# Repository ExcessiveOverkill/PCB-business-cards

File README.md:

# Persistence of vision display business cards

PCB cards designed for opensauce 2024 to give out to people

## Who is this repo for?
Anyone looking to make these cards for themselves or their own business.
It is NOT for people looking to make and sell the cards to others. (non-commercial use only)

## Software
- STM32CubeIDE
- python (numpy, cv2)
- Visual Studio Code

## Assembly
### The boards themselves
I ordered my PCBs from PCB way with .8mm thickness and ENIG coating since it is important to have a good contact surface for the batteries (and it looks nicer than HASL)

### Components
> [!WARNING]
> These exact parts I ordered in bulk from LCSC.
> The parts below are the closest matches I could find from DigiKey, but have not been tested yet

A DigiKey cart containing all of the needed components can be found [here](https://www.digikey.com/en/mylists/list/D8ND2J1IRM)
> [!IMPORTANT]
> The battery clips I used were from LCSC not DigiKey. The ones in the digikey cart have a slightly different footprint and may not fit perfectly.
> The exact clips I used can be found [here](https://www.lcsc.com/product-detail/Button-And-Strip-Battery-Connector_MYOUNG-MY-2032-30_C7525432.html)

Two standard CR2032 batteries are required, I used the cheap amazon ones.

### Placement
An interactive BOM can be found [here](opensauce2024/bom/ibom.html) (open in browser)

### Soldering
These boards are NOT designed to be hand-solderable.

I highly recommend at least a hotplate.

A stencil could be purchaced from a PCB manufacturer to make placing the solder paste easier, but it is not requred. (PCB and stencil files are in the repo)

The accelerometer is very susceptible to bad solder joints and will result in the card not activating when shaken. I had to resolder many of them to fix this.

## Programming
### Generating the graphics
Run "imageConverter.py", select which images or animations you want to display normally.

A second file select window will open for SECRET images to display. They will be displayed randomly according to the parameters set at the top of the python file.

Simply don't select anything if you do not want a secret image.

Images should be 32 pixel high PNGs, width does not matter, the card will show the entire image.

Once the images are selected, the program will show a demo of what will be displayed then write to a file defining the frame data.

### Programming the card
After the graphics have been saved, you simply build and upload the STM32 project using STM32CubeIDE.

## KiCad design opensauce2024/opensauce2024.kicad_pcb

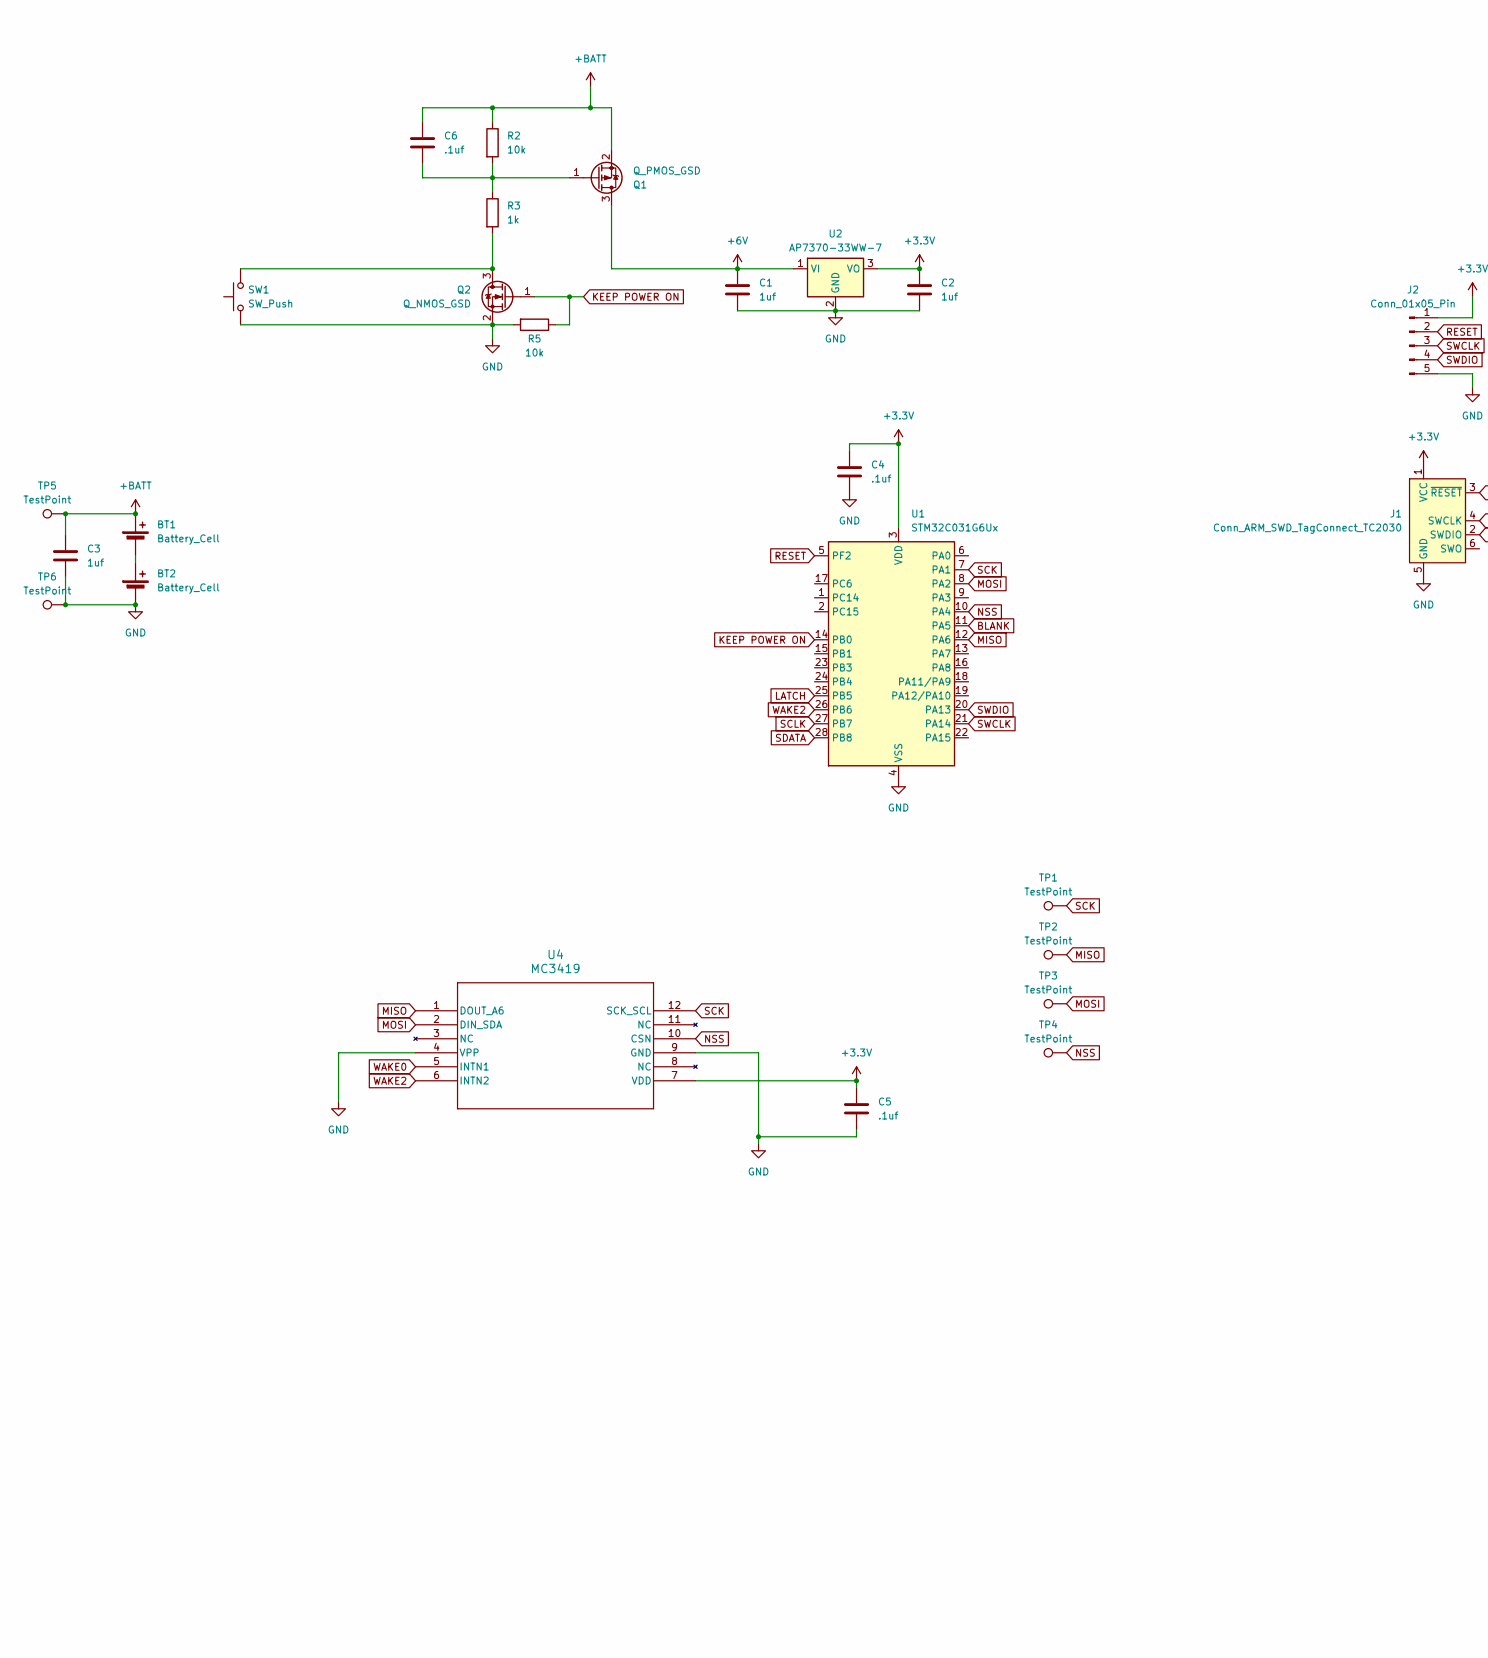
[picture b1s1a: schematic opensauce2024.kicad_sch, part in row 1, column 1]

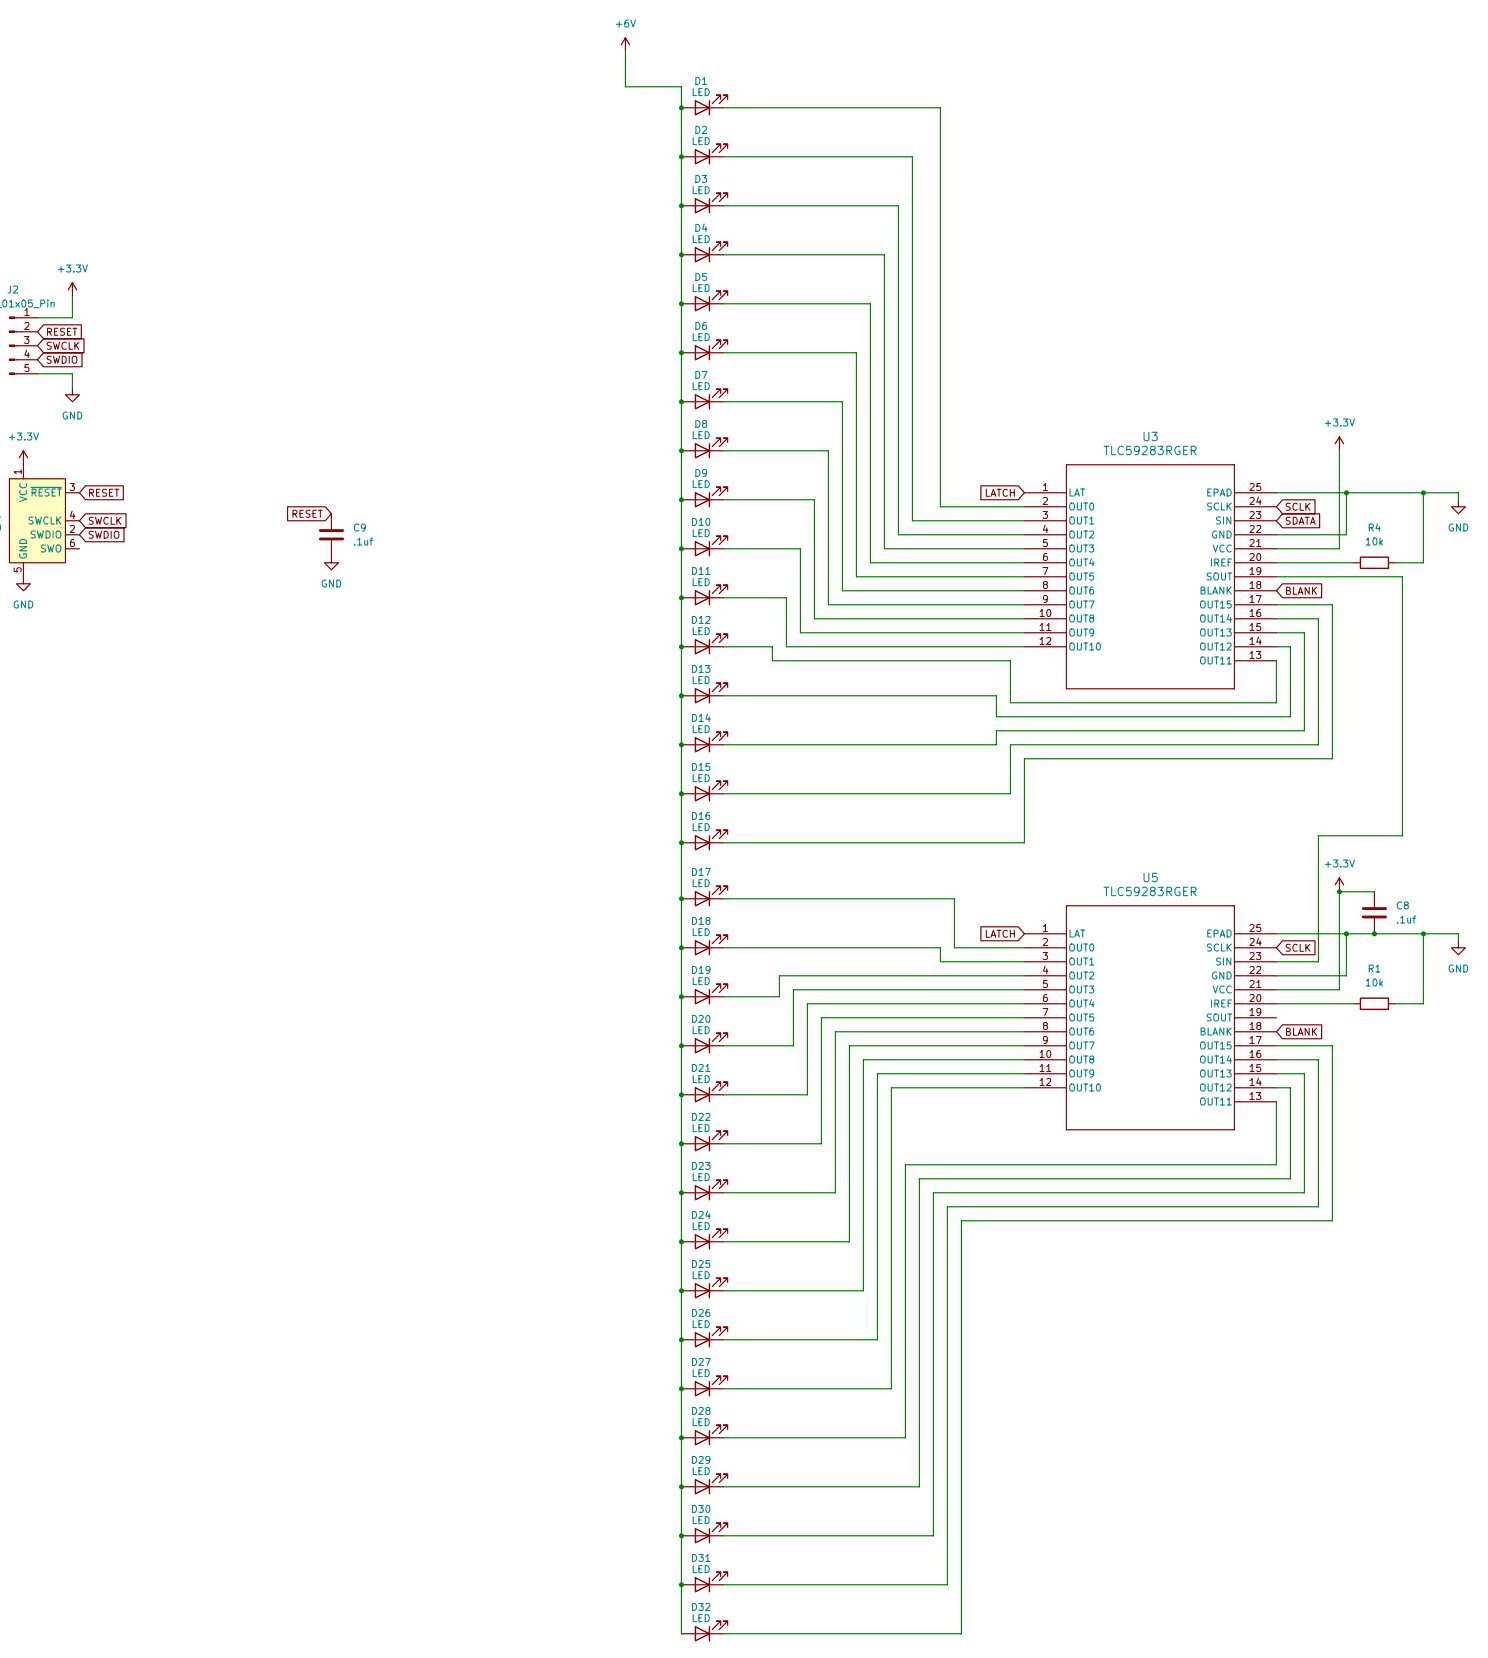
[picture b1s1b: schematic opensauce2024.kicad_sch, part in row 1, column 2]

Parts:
BT1, BT2: Battery_Cell; cr2032
C1, C2, C3: 1uf; C_0603_1608Metric
C4, C5, C6, C8, C9: .1uf; C_0603_1608Metric
D1, D2, D3, D4, D5, D6, D7, D8, D9, D10, D11, D12, D13, D14, D15, D16, D17, D18, D19, D20, D21, D22, D23, D24, D25, D26, D27, D28, D29, D30, D31, D32: LED; LED_0603_1608Metric
J1: Conn_ARM_SWD_TagConnect_TC2030; Tag-Connect_TC2030-IDC-FP_2x03_P1.27mm_Vertical
J2: Conn_01x05_Pin; PinHeader_1x05_P2.54mm_Vertical
Q1: Q_PMOS_GSD; SOT-23
Q2: Q_NMOS_GSD; SOT-23
R1, R2, R4, R5: 10k; R_0603_1608Metric
R3: 1k; R_0603_1608Metric
SW1: SW_Push; SW_Push_1P1T_XKB_TS-1187A
TP1, TP2, TP3, TP4: TestPoint; TestPoint_Pad_D1.0mm
TP5, TP6: TestPoint; TestPoint_Pad_D2.0mm
U1: STM32C031G6Ux; QFN-28_4x4mm_P0.5mm
U2: AP7370-33WW-7; SOT25
U3, U5: TLC59283RGER; RGE24_2P1X2P1_TEX
U4: MC3419; LGA-12_2x2mm_P0.5mm

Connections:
+3.3V: C2.1, C4.1, C5.1, C8.1, J1.1 (VCC), J2.1, U1.3 (VDD), U2.3 (VO), U3.21 (VCC), U4.7 (VDD), U5.21 (VCC)
+6V: C1.1, D1.2 (A), D2.2 (A), D3.2 (A), D4.2 (A), D5.2 (A), D6.2 (A), D7.2 (A), D8.2 (A), D9.2 (A), D10.2 (A), D11.2 (A), D12.2 (A), D13.2 (A), D14.2 (A), D15.2 (A), D16.2 (A), D17.2 (A), D18.2 (A), D19.2 (A), D20.2 (A), D21.2 (A), D22.2 (A), D23.2 (A), D24.2 (A), D25.2 (A), D26.2 (A), D27.2 (A), D28.2 (A), D29.2 (A), D30.2 (A), D31.2 (A), D32.2 (A), Q1.3 (D), U2.1 (VI)
+BATT: BT1.1 (+), C3.1, C6.1, Q1.2 (S), R2.1, TP5.1
BLANK: U1.11 (PA5), U3.18 (BLANK), U5.18 (BLANK)
GND: BT2.2 (-), C1.2, C2.2, C3.2, C4.2, C5.2, C8.2, C9.2, J1.5 (GND), J2.5, Q2.2 (S), R1.2, R4.2, R5.2, SW1.1, TP6.1, U1.4 (VSS), U2.2 (GND), U3.22 (GND), U3.25 (EPAD), U4.4 (VPP), U4.9 (GND), U5.22 (GND), U5.25 (EPAD)
KEEP POWER ON: Q2.1 (G), R5.1, U1.14 (PB0)
LATCH: U1.25 (PB5), U3.1 (LAT), U5.1 (LAT)
MISO: TP2.1, U1.12 (PA6), U4.1 (DOUT_A6)
MOSI: TP3.1, U1.8 (PA2), U4.2 (DIN_SDA)
NSS: TP4.1, U1.10 (PA4), U4.10 (CSN)
unnamed: BT1.2 (-), BT2.1 (+)
unnamed: D1.1 (K), U3.2 (OUT0)
unnamed: D2.1 (K), U3.3 (OUT1)
unnamed: D3.1 (K), U3.4 (OUT2)
unnamed: D4.1 (K), U3.5 (OUT3)
unnamed: D5.1 (K), U3.6 (OUT4)
unnamed: D6.1 (K), U3.7 (OUT5)
unnamed: D7.1 (K), U3.8 (OUT6)
unnamed: D8.1 (K), U3.9 (OUT7)
unnamed: D9.1 (K), U3.10 (OUT8)
unnamed: D10.1 (K), U3.11 (OUT9)
unnamed: D11.1 (K), U3.12 (OUT10)
unnamed: D12.1 (K), U3.13 (OUT11)
unnamed: D13.1 (K), U3.14 (OUT12)
unnamed: D14.1 (K), U3.15 (OUT13)
unnamed: D15.1 (K), U3.16 (OUT14)
unnamed: D16.1 (K), U3.17 (OUT15)
unnamed: D17.1 (K), U5.2 (OUT0)
unnamed: D18.1 (K), U5.3 (OUT1)
unnamed: D19.1 (K), U5.4 (OUT2)
unnamed: D20.1 (K), U5.5 (OUT3)
unnamed: D21.1 (K), U5.6 (OUT4)
unnamed: D22.1 (K), U5.7 (OUT5)
unnamed: D23.1 (K), U5.8 (OUT6)
unnamed: D24.1 (K), U5.9 (OUT7)
unnamed: D25.1 (K), U5.10 (OUT8)
unnamed: D26.1 (K), U5.11 (OUT9)
unnamed: D27.1 (K), U5.12 (OUT10)
unnamed: D28.1 (K), U5.13 (OUT11)
unnamed: D29.1 (K), U5.14 (OUT12)
unnamed: D30.1 (K), U5.15 (OUT13)
unnamed: D31.1 (K), U5.16 (OUT14)
unnamed: D32.1 (K), U5.17 (OUT15)
unnamed: C6.2, Q1.1 (G), R2.2, R3.1
unnamed: Q2.3 (D), R3.2, SW1.2
unnamed: R4.1, U3.20 (IREF)
unnamed: U3.19 (SOUT), U5.23 (SIN)
unnamed: R1.1, U5.20 (IREF)
RESET: C9.1, J1.3 (~RESET), J2.2, U1.5 (PF2)
SCK: TP1.1, U1.7 (PA1), U4.12 (SCK_SCL)
SCLK: U1.27 (PB7), U3.24 (SCLK), U5.24 (SCLK)
SDATA: U1.28 (PB8), U3.23 (SIN)
SWCLK: J1.4 (SWCLK), J2.3, U1.21 (PA14)
SWDIO: J1.2 (SWDIO), J2.4, U1.20 (PA13)
WAKE0: U4.5 (INTN1)
WAKE2: U1.26 (PB6), U4.6 (INTN2)

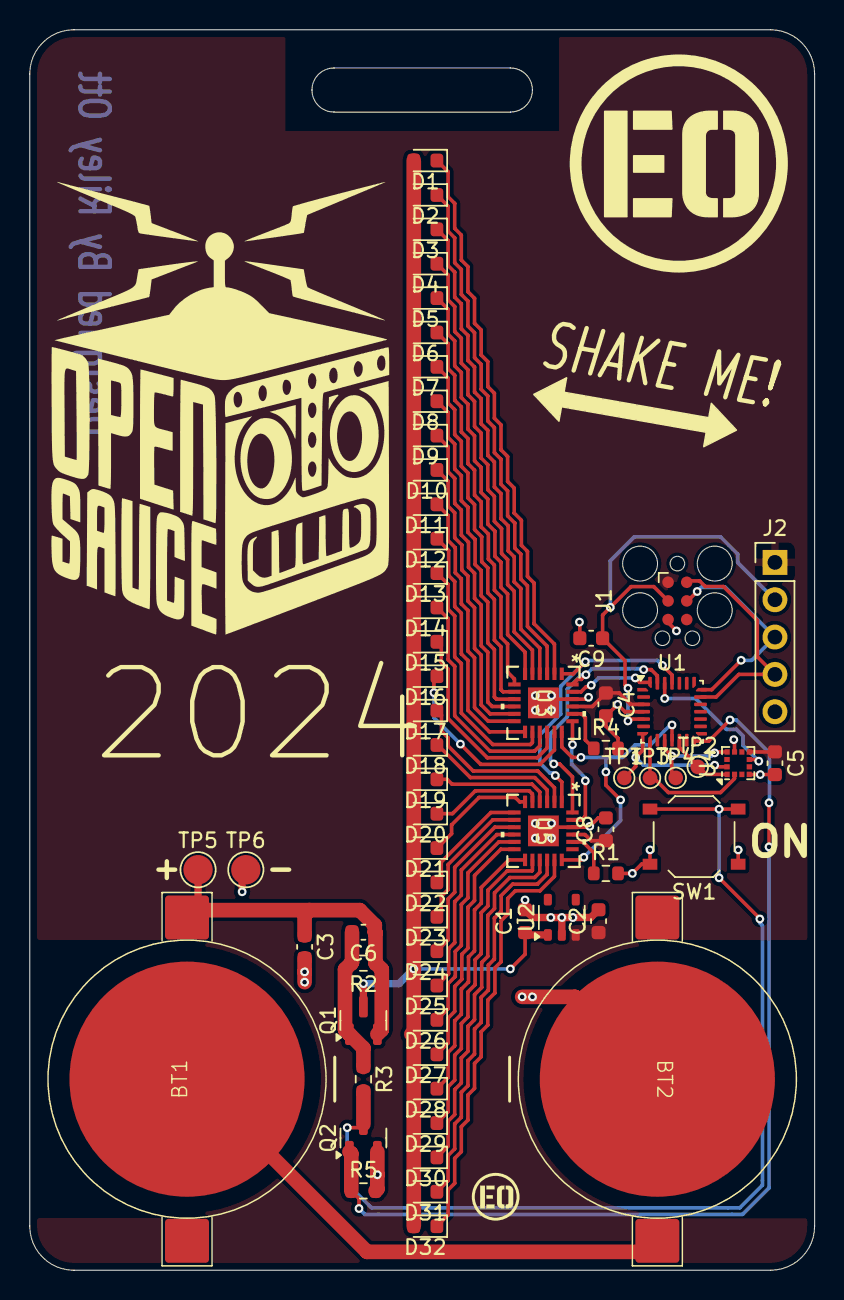
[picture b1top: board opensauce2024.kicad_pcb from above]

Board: 2 copper layers, 53.4 x 84.4 mm, 63 parts (0 on the bottom side), 55 nets.

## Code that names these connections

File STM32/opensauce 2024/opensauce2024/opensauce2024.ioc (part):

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Mcu.Name=STM32C031G(4-6)Ux
Mcu.Package=UFQFPN28
Mcu.UserName=STM32C031G6Ux
PA1.GPIOParameters=GPIO_Speed,PinState
PA1.GPIO_Speed=GPIO_SPEED_FREQ_HIGH
PA1.Mode=Full_Duplex_Master
PA1.PinState=GPIO_PIN_SET
PA1.Signal=SPI1_SCK
PA13.Mode=Serial_Wire
PA13.Signal=DEBUG_SWDIO
PA14-BOOT0.Mode=Serial_Wire
PA14-BOOT0.Signal=DEBUG_SWCLK
PA2.GPIOParameters=GPIO_Speed
PA2.GPIO_Speed=GPIO_SPEED_FREQ_HIGH
PA2.Mode=Full_Duplex_Master
PA2.Signal=SPI1_MOSI
PA4.GPIOParameters=GPIO_Speed,PinState,GPIO_Label
PA4.GPIO_Label=ACCEL_SELECT
PA4.GPIO_Speed=GPIO_SPEED_FREQ_MEDIUM
PA4.PinState=GPIO_PIN_SET
PA4.Signal=GPIO_Output
PA5.GPIOParameters=GPIO_Speed,GPIO_Label
PA5.GPIO_Label=LED BLANK
PA5.GPIO_Speed=GPIO_SPEED_FREQ_LOW
PA5.Signal=GPIO_Output
PA6.GPIOParameters=GPIO_Speed,GPIO_PuPd
PA6.GPIO_PuPd=GPIO_NOPULL
PA6.GPIO_Speed=GPIO_SPEED_FREQ_HIGH
PA6.Mode=Full_Duplex_Master
PA6.Signal=SPI1_MISO
PB0.GPIOParameters=GPIO_Speed,GPIO_Label
PB0.GPIO_Label=KEEP POWER ON
PB0.GPIO_Speed=GPIO_SPEED_FREQ_LOW
PB0.Signal=GPIO_Output
PB5.GPIOParameters=GPIO_Speed,GPIO_Label
PB5.GPIO_Label=LED DATA LATCH
PB5.GPIO_Speed=GPIO_SPEED_FREQ_MEDIUM
PB5.Signal=GPIO_Output
PB6.GPIOParameters=GPIO_Label
PB6.GPIO_Label=ACCEL_INTERRUPT
PB6.Signal=GPIO_Input
PB7.GPIOParameters=GPIO_Speed,GPIO_Label,GPIO_FM7
PB7.GPIO_FM7=SYSCFG_FASTMODEPLUS_PB7
PB7.GPIO_Label=LED DATA CLOCK
PB7.GPIO_Speed=GPIO_SPEED_FREQ_MEDIUM
PB7.Signal=GPIO_Output
PB8.GPIOParameters=GPIO_Speed,GPIO_Label,GPIO_FM8
PB8.GPIO_FM8=SYSCFG_FASTMODEPLUS_PB8
PB8.GPIO_Label=LED DATA
PB8.GPIO_Speed=GPIO_SPEED_FREQ_MEDIUM
PB8.Signal=GPIO_Output
RCC.HSE_VALUE=8000000
RCC.SYSCLKFreq_VALUE=48000000
board=custom

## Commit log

2024-06-07 Add all files
2024-06-10 add new animations
2024-06-23 Create PCB-business-cards.code-workspace
